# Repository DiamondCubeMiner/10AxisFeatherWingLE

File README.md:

# 10AxisFeatherWingLE #
A 10-DOF Featherwing, powered by LSM9DS1 and BMP280.

## Description ##
This featherwing uses I2C to connect both the IMU (LSM9DS1) and the altimeter (BMP280) to the Feather.
I made this to design projects that require a 10-DOF IMU in a tiny package where breakouts can affect the weight a lot and may not be a good option, such as a quadcopter, a model plane, or a model rocket.

## Drivers ##
These drivers should work as the project is a derivative of SparkFun hardware:
  - [SparkFun_LSM9DS1_Arduino_Library](https://github.com/sparkfun/SparkFun_LSM9DS1_Arduino_Library)
  - [SparkFun_BME280_Arduino_Library](https://github.com/sparkfun/SparkFun_BME280_Arduino_Library)

## Thanks ##
This project is derived from the following projects:
  - [SparkFun 9DoF Sensor Stick](https://github.com/sparkfun/9DOF_Sensor_Stick)
  - [SparkFun Atmospheric Sensor Breakout - BME280 (Qwiic)](https://github.com/sparkfun/Qwiic_Atmospheric_Sensor_Breakout_BME280)

Thanks to Sparkfun for their open-source schematics and libraries!

## License ##
This work is licensed under the Creative Commons Attribution-ShareAlike 4.0 International License. To view a copy of this license, visit http://creativecommons.org/licenses/by-sa/4.0/ or send a letter to Creative Commons, PO Box 1866, Mountain View, CA 94042, USA.

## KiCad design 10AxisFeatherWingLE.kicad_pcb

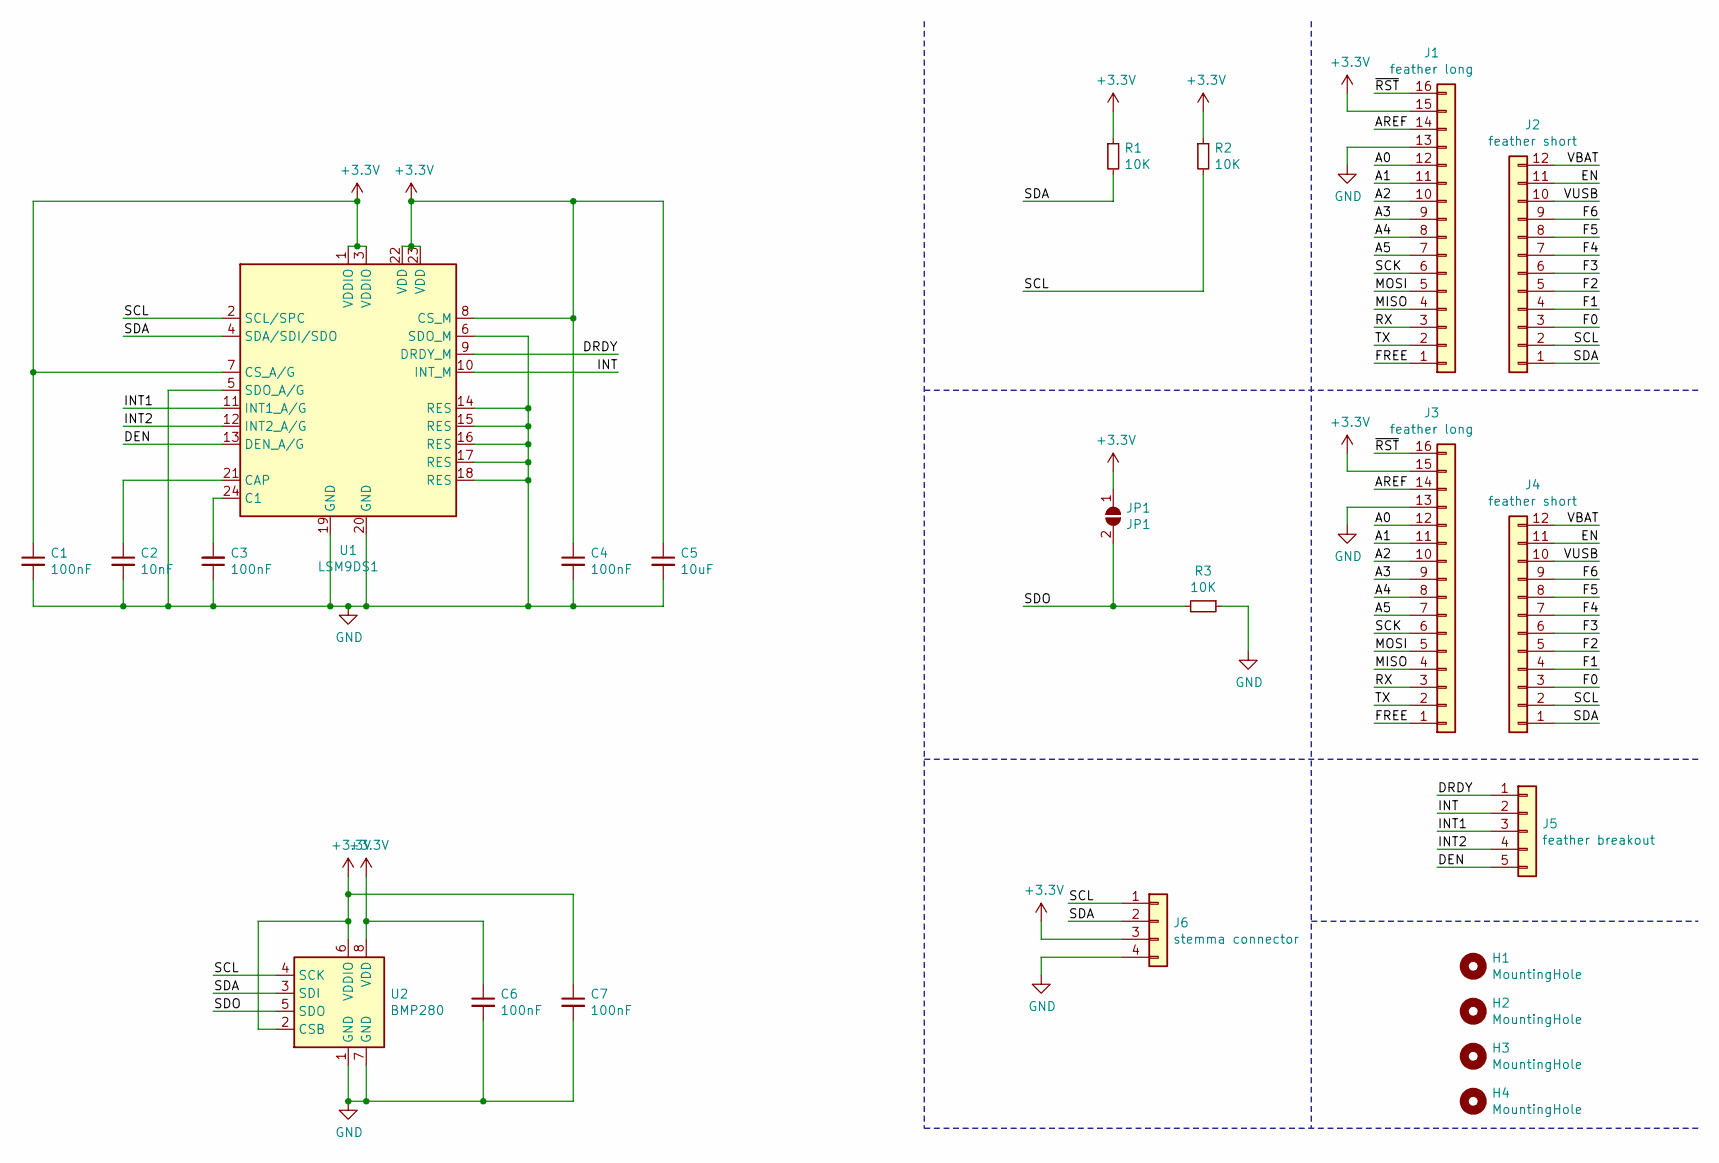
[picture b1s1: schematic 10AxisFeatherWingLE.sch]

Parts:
C1, C3, C4, C6, C7: 100nF; C_0603_1608Metric
C2: 10nF; C_0603_1608Metric
C5: 10uF; C_0603_1608Metric
H1, H2, H3, H4: MountingHole; MountingHole_2.7mm_M2.5
J1: feather long; PinHeader_1x16_P2.54mm_Vertical
J2: feather short; PinHeader_1x12_P2.54mm_Vertical
J3: feather long; PinSocket_1x16_P2.54mm_Vertical
J4: feather short; PinSocket_1x12_P2.54mm_Vertical
J5: feather breakout; PinHeader_1x05_P2.54mm_Vertical
J6: stemma connector; JST_PH_B4B-PH-K_1x04_P2.00mm_Vertical
JP1: JP1; SolderJumper-2_P1.3mm_Open_Pad1.0x1.5mm
R1, R2, R3: 10K; R_0603_1608Metric
U1: LSM9DS1; LGA-24L_3x3.5mm_P0.43mm
U2: BMP280; Bosch_LGA-8_2x2.5mm_P0.65mm_ClockwisePinNumbering

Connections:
+3V3: C1.1, C4.1, C5.1, C6.1, C7.1, J1.15, J3.15, J6.3, JP1.1 (A), R1.1, R2.1, U1.1 (VDDIO), U1.3 (VDDIO), U1.7 (CS_A/G), U1.8 (CS_M), U1.22 (VDD), U1.23 (VDD), U2.2 (CSB), U2.6 (VDDIO), U2.8 (VDD)
/A0: J1.12, J3.12
/A1: J1.11, J3.11
/A2: J1.10, J3.10
/A3: J1.9, J3.9
/A4: J1.8, J3.8
/A5: J1.7, J3.7
/AREF: J1.14, J3.14
/DEN: J5.5, U1.13 (DEN_A/G)
/DRDY: J5.1, U1.9 (DRDY_M)
/EN: J2.11, J4.11
/F0: J2.3, J4.3
/F1: J2.4, J4.4
/F2: J2.5, J4.5
/F3: J2.6, J4.6
/F4: J2.7, J4.7
/F5: J2.8, J4.8
/F6: J2.9, J4.9
/FREE: J1.1, J3.1
/INT: J5.2, U1.10 (INT_M)
/INT1: J5.3, U1.11 (INT1_A/G)
/INT2: J5.4, U1.12 (INT2_A/G)
/MISO: J1.4, J3.4
/MOSI: J1.5, J3.5
/RX: J1.3, J3.3
/SCK: J1.6, J3.6
/SCL: J2.2, J4.2, J6.1, R2.2, U1.2 (SCL/SPC), U2.4 (SCK)
/SDA: J2.1, J4.1, J6.2, R1.2, U1.4 (SDA/SDI/SDO), U2.3 (SDI)
/SDO: JP1.2 (B), R3.2, U2.5 (SDO)
/TX: J1.2, J3.2
/VBAT: J2.12, J4.12
/VUSB: J2.10, J4.10
/~RST: J1.16, J3.16
GND: C1.2, C2.2, C3.1, C4.2, C5.2, C6.2, C7.2, J1.13, J3.13, J6.4, R3.1, U1.5 (SDO_A/G), U1.6 (SDO_M), U1.14 (RES), U1.15 (RES), U1.16 (RES), U1.17 (RES), U1.18 (RES), U1.19 (GND), U1.20 (GND), U2.1 (GND), U2.7 (GND)
unnamed: C2.1, U1.21 (CAP)
unnamed: C3.2, U1.24 (C1)

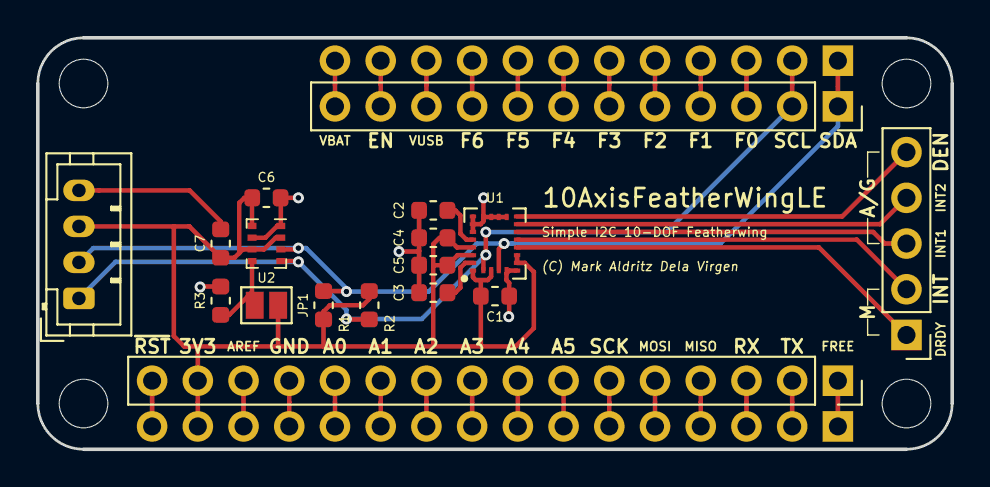
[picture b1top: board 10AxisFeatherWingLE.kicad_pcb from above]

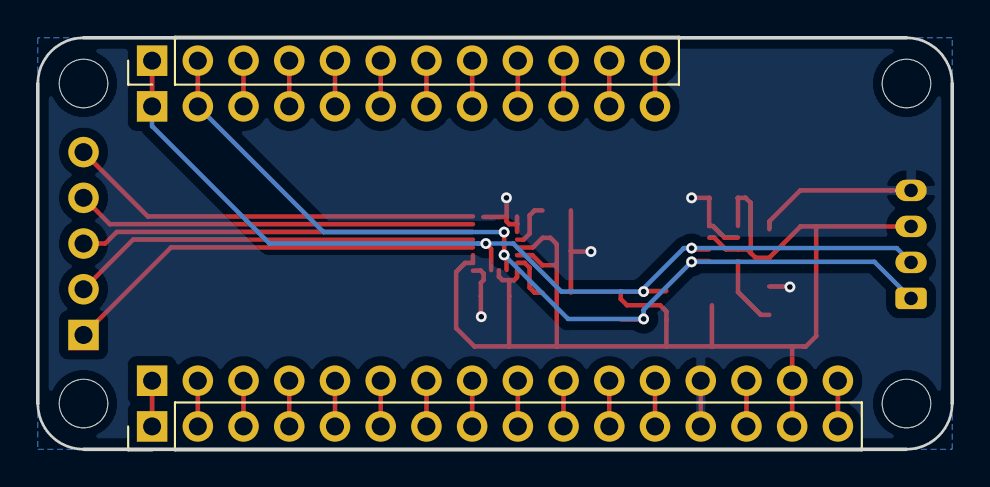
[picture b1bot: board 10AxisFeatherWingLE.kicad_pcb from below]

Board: 2 copper layers, 50.8 x 22.9 mm, 23 parts (2 on the bottom side), 36 nets.

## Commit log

2019-12-22 Initial upload
2019-12-24 Added new features
    Added breakouts and silk text.
2019-12-26 Board silk edit
2019-12-31 Migration to KiCad
2020-01-05 Corrected capacitor values
    CAP and C1 capacitors were flipped, fixed
2020-01-07 Minor format fix
2020-01-12 Increased trace width
2020-01-17 Changed grove connector to STEMMA
2020-02-06 Removed STEMMA connector
    STEMMA requires the use of a 3.3V to 5V level shifter and voltage regulator.
    The board does not support these features, so they were removed.
2020-11-18 Eagle Refactor
    Remade the project in EAGLE. Needs signal routing.
2021-01-26 Added traces
    Added traces to board file.
